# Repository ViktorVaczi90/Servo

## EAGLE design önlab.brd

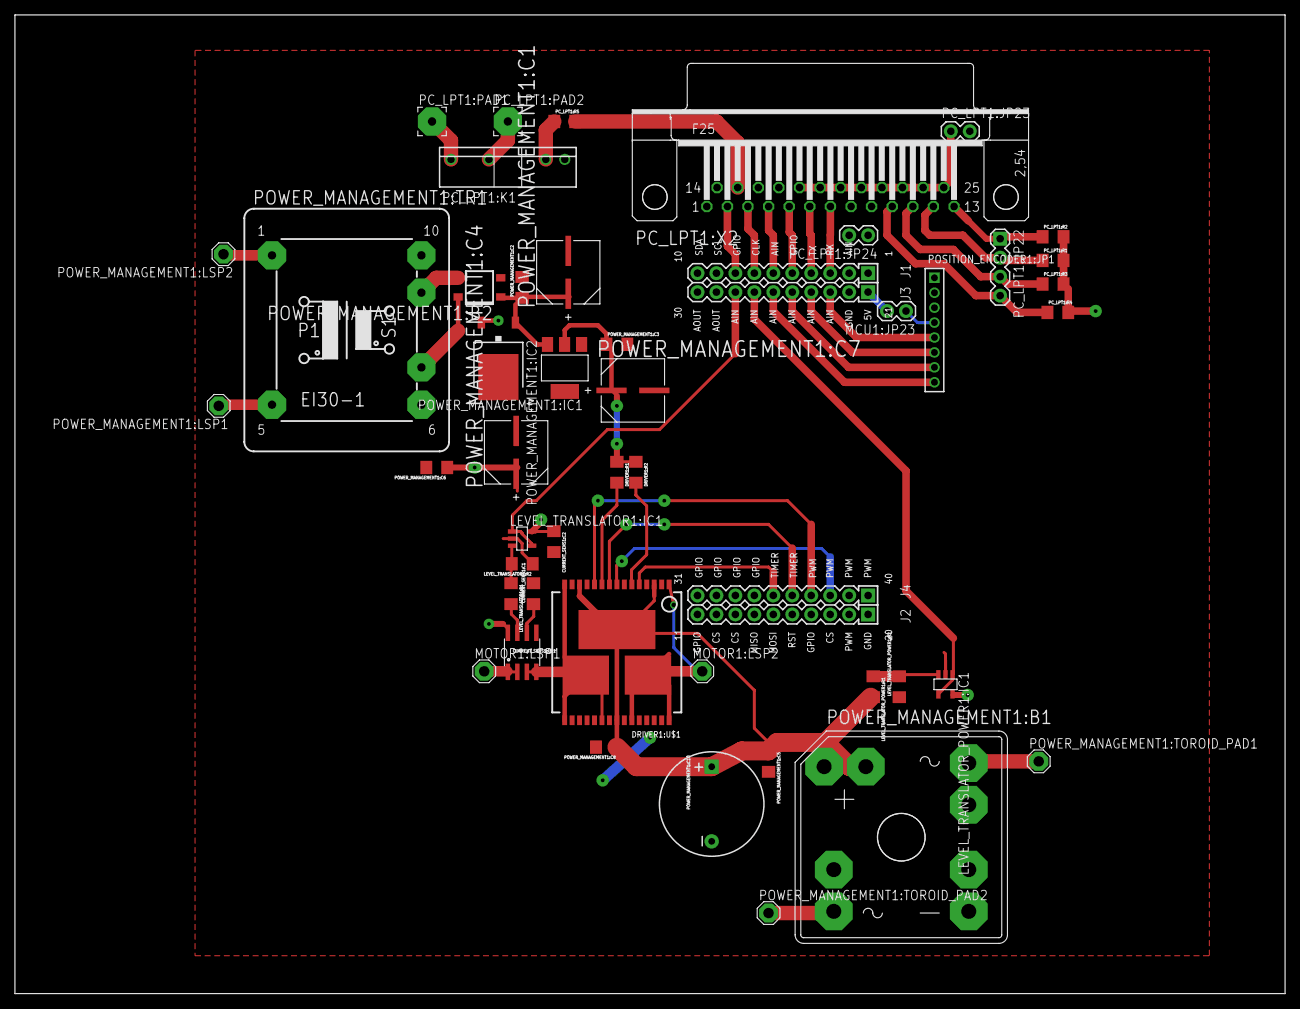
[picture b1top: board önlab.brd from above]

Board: 2 copper layers, 170.2 x 131.1 mm, 47 parts (0 on the bottom side), 48 nets.

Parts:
CURRENT_SENS1:C1: 1nF; 1206
CURRENT_SENS1:C2: 100nF; 1206
CURRENT_SENS1:U$1: ACS712; SO08
DRIVER1:R1, DRIVER1:R2: 5k; 1206
DRIVER1:U$1: VNH2SP30
LEVEL_TRANSLATOR1:IC1: OPA340N; SOT23-5
LEVEL_TRANSLATOR1:R1: 1.8k; 1206
LEVEL_TRANSLATOR1:R2: 3.3k; 1206
LEVEL_TRANSLATOR_POWER1:IC1: OPA340N; SOT23-5
LEVEL_TRANSLATOR_POWER1:R1: 20k; 1206
LEVEL_TRANSLATOR_POWER1:R2: 1.8k; 1206
MCU1:A1: 4X10-BOOSTERPACK
MCU1:JP23: 1X02
MOTOR1:LSP1, MOTOR1:LSP2: SE14
PC_LPT1:JP22: 1X04
PC_LPT1:JP23, PC_LPT1:JP24: 1X02
PC_LPT1:K1: S202S02
PC_LPT1:PAD1, PC_LPT1:PAD2: 3,81/1,1
PC_LPT1:R1, PC_LPT1:R2, PC_LPT1:R3, PC_LPT1:R4, PC_LPT1:R5: 5k; 1206
PC_LPT1:X2: F25H
POSITION_ENCODER1:JP1: 1X08M
POWER_MANAGEMENT1:B1: B25A-
POWER_MANAGEMENT1:B2: RECTIFIER-S380; TO-269AA
POWER_MANAGEMENT1:C1, POWER_MANAGEMENT1:C4, POWER_MANAGEMENT1:C7: 220UF; CAPAE830X650N
POWER_MANAGEMENT1:C2, POWER_MANAGEMENT1:C3, POWER_MANAGEMENT1:C5, POWER_MANAGEMENT1:C6, POWER_MANAGEMENT1:C8: 100nF; 1206
POWER_MANAGEMENT1:C10: 1000uf/25V; CPOL_RM10
POWER_MANAGEMENT1:IC1: REG1117; SOT223
POWER_MANAGEMENT1:IC2: 7805DT; TO252
POWER_MANAGEMENT1:LSP1, POWER_MANAGEMENT1:LSP2, POWER_MANAGEMENT1:TOROID_PAD1, POWER_MANAGEMENT1:TOROID_PAD2: SE14
POWER_MANAGEMENT1:TR1: 220/9; EI30-1

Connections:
3.3V: DRIVER1:R1.1, DRIVER1:R2.1, POWER_MANAGEMENT1:C3.1, POWER_MANAGEMENT1:C7.1, POWER_MANAGEMENT1:IC1.2
5V: CURRENT_SENS1:C2.1, CURRENT_SENS1:U$1.8, LEVEL_TRANSLATOR1:IC1.5, LEVEL_TRANSLATOR_POWER1:IC1.5, MCU1:JP23.1, PC_LPT1:R1.2, PC_LPT1:R2.2, PC_LPT1:R3.2, PC_LPT1:R4.2, POSITION_ENCODER1:JP1.4, POWER_MANAGEMENT1:C4.1, POWER_MANAGEMENT1:C6.1, POWER_MANAGEMENT1:IC2.2
CS1: DRIVER1:U$1.9, MCU1:A1.36
CURRENT_SENS1:N$1: CURRENT_SENS1:C1.1, CURRENT_SENS1:U$1.6
DRIVER1:DIAG_A/EN_A: DRIVER1:R2.2, DRIVER1:U$1.6
DRIVER1:DIAG_B/EN_B: DRIVER1:R1.2, DRIVER1:U$1.10
GND: CURRENT_SENS1:C1.2, CURRENT_SENS1:C2.2, CURRENT_SENS1:U$1.5, DRIVER1:U$1.18, DRIVER1:U$1.19, DRIVER1:U$1.20, DRIVER1:U$1.26, DRIVER1:U$1.27, DRIVER1:U$1.28, LEVEL_TRANSLATOR1:IC1.2, LEVEL_TRANSLATOR1:R2.1, LEVEL_TRANSLATOR_POWER1:IC1.2, LEVEL_TRANSLATOR_POWER1:R2.1, MCU1:A1.20, MCU1:A1.22, PC_LPT1:JP23.2, PC_LPT1:K1.4, POSITION_ENCODER1:JP1.3, POWER_MANAGEMENT1:B1.-1, POWER_MANAGEMENT1:B2.-, POWER_MANAGEMENT1:C1.2, POWER_MANAGEMENT1:C2.2, POWER_MANAGEMENT1:C3.2, POWER_MANAGEMENT1:C4.2, POWER_MANAGEMENT1:C5.2, POWER_MANAGEMENT1:C6.2, POWER_MANAGEMENT1:C7.2, POWER_MANAGEMENT1:C8.2, POWER_MANAGEMENT1:C10.-, POWER_MANAGEMENT1:IC1.1, POWER_MANAGEMENT1:IC2.3
LEVEL_TRANSLATOR1:N$1: LEVEL_TRANSLATOR1:IC1.3, LEVEL_TRANSLATOR1:R1.1, LEVEL_TRANSLATOR1:R2.2
LEVEL_TRANSLATOR_POWER1:N$1: LEVEL_TRANSLATOR_POWER1:IC1.3, LEVEL_TRANSLATOR_POWER1:R1.1, LEVEL_TRANSLATOR_POWER1:R2.2
MCU1:N$1: MCU1:A1.21, MCU1:JP23.2
unnamed: MCU1:A1.3, PC_LPT1:X2.7
unnamed: MCU1:A1.4, PC_LPT1:X2.6
unnamed: MCU1:A1.6, PC_LPT1:X2.4
unnamed: MCU1:A1.5, PC_LPT1:X2.5
unnamed: MCU1:A1.8, PC_LPT1:X2.2
unnamed: MCU1:A1.7, PC_LPT1:X2.3
unnamed: LEVEL_TRANSLATOR1:IC1.1, LEVEL_TRANSLATOR1:IC1.4, MCU1:A1.28
unnamed: CURRENT_SENS1:U$1.3, CURRENT_SENS1:U$1.4, DRIVER1:U$1.15, DRIVER1:U$1.16, DRIVER1:U$1.21, DRIVER1:U$1.SLUG2
unnamed: DRIVER1:U$1.1, DRIVER1:U$1.25, DRIVER1:U$1.30, DRIVER1:U$1.SLUG3, MOTOR1:LSP2.MP
unnamed: CURRENT_SENS1:U$1.1, CURRENT_SENS1:U$1.2, MOTOR1:LSP1.MP
unnamed: CURRENT_SENS1:U$1.7, LEVEL_TRANSLATOR1:R1.2
unnamed: MCU1:A1.25, POSITION_ENCODER1:JP1.7
unnamed: MCU1:A1.23, POSITION_ENCODER1:JP1.5
unnamed: MCU1:A1.26, POSITION_ENCODER1:JP1.8
unnamed: MCU1:A1.24, POSITION_ENCODER1:JP1.6
OUT_A1: DRIVER1:U$1.5, MCU1:A1.35
OUT_B1: DRIVER1:U$1.11, MCU1:A1.37
PC_LPT1:N$12: PC_LPT1:JP22.4, PC_LPT1:R4.1, PC_LPT1:X2.10
PC_LPT1:N$28: PC_LPT1:JP22.3, PC_LPT1:R3.1, PC_LPT1:X2.11
PC_LPT1:N$31: PC_LPT1:JP22.2, PC_LPT1:R1.1, PC_LPT1:X2.12
PC_LPT1:N$34: PC_LPT1:JP22.1, PC_LPT1:R2.1, PC_LPT1:X2.13
PC_LPT1:N$41: PC_LPT1:K1.3, PC_LPT1:R5.1
PC_LPT1:N$42: PC_LPT1:R5.2, PC_LPT1:X2.15
PC_LPT1:N$43: PC_LPT1:K1.2, PC_LPT1:PAD2.1
PC_LPT1:N$44: PC_LPT1:K1.1, PC_LPT1:PAD1.1
PC_LPT1:N$45: PC_LPT1:JP24.1, PC_LPT1:X2.9
PC_LPT1:N$46: PC_LPT1:JP24.2, PC_LPT1:X2.8
PC_LPT1:PRE_GND: PC_LPT1:JP23.1, PC_LPT1:X2.18, PC_LPT1:X2.19, PC_LPT1:X2.20, PC_LPT1:X2.21, PC_LPT1:X2.22, PC_LPT1:X2.23, PC_LPT1:X2.24, PC_LPT1:X2.25
POWER_MANAGEMENT1:N$1: POWER_MANAGEMENT1:B1.AC2-, POWER_MANAGEMENT1:TOROID_PAD2.MP
POWER_MANAGEMENT1:N$2: POWER_MANAGEMENT1:B1.AC1-, POWER_MANAGEMENT1:TOROID_PAD1.MP
POWER_MANAGEMENT1:N$3: POWER_MANAGEMENT1:B2.AC1, POWER_MANAGEMENT1:TR1.7
POWER_MANAGEMENT1:N$4: POWER_MANAGEMENT1:B2.AC2, POWER_MANAGEMENT1:TR1.9
POWER_MANAGEMENT1:N$7: POWER_MANAGEMENT1:LSP2.MP, POWER_MANAGEMENT1:TR1.1
POWER_MANAGEMENT1:N$8: POWER_MANAGEMENT1:LSP1.MP, POWER_MANAGEMENT1:TR1.5
POWER_MANAGEMENT1:REC9V: POWER_MANAGEMENT1:B2.+, POWER_MANAGEMENT1:C1.1, POWER_MANAGEMENT1:C2.1, POWER_MANAGEMENT1:IC1.3, POWER_MANAGEMENT1:IC2.1
PWM1: DRIVER1:U$1.8, MCU1:A1.38
VCC: DRIVER1:U$1.3, DRIVER1:U$1.13, DRIVER1:U$1.23, DRIVER1:U$1.SLUG1, LEVEL_TRANSLATOR_POWER1:R1.2, POWER_MANAGEMENT1:B1.+1, POWER_MANAGEMENT1:C5.1, POWER_MANAGEMENT1:C8.1, POWER_MANAGEMENT1:C10.+
VCC_SENSE: LEVEL_TRANSLATOR_POWER1:IC1.1, LEVEL_TRANSLATOR_POWER1:IC1.4, MCU1:A1.27

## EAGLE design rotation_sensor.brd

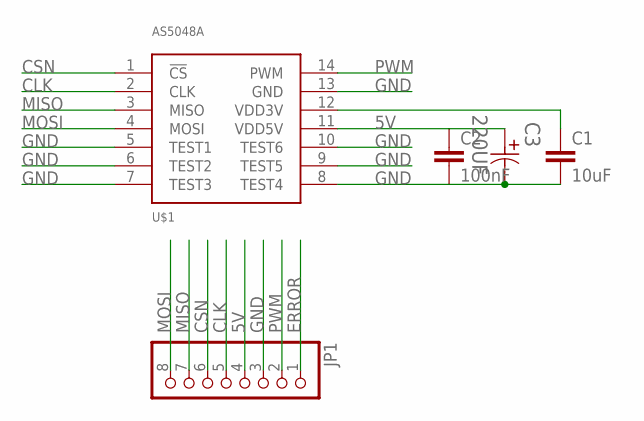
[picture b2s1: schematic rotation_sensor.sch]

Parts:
C1: 10uF; 1206
C2: 100nF; 1206
C3: 220UF; CAPAE830X650N
JP1: PINHD-1X8M; 1X08M
U$1: AS5048A; TSSOP14

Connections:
5V: C2.1, C3.1, JP1.4, U$1.11 (VDD5V)
CLK: JP1.5, U$1.2 (CLK)
CSN: JP1.6, U$1.1 (!CS)
ERROR: JP1.1
GND: C1.2, C2.2, C3.2, JP1.3, U$1.5 (TEST1), U$1.6 (TEST2), U$1.7 (TEST3), U$1.8 (TEST4), U$1.9 (TEST5), U$1.10 (TEST6), U$1.13 (GND)
MISO: JP1.7, U$1.3 (MISO)
MOSI: JP1.8, U$1.4 (MOSI)
unnamed: C1.1, U$1.12 (VDD3V)
PWM: JP1.2, U$1.14 (PWM)

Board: 2 copper layers, 5 parts (0 on the bottom side), 8 nets, no tracks yet.

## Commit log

2015-05-12 first prototype

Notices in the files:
parts and their libraries:
SparkFun-Passives: Licensing: Creative Commons ShareAlike 4.0 International - https://creativecommons.org/licenses/by-sa/4.0
